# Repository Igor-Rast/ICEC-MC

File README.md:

# ICEC-MC
ICEC-MC Cape for BeagleBone Black

## Introduction
ICEC-MC is a project to create the plans, prototype board and software for a completly Open Source Motor Controller board in the form of a Cape that can be placed on a BeagleBone Black.
The ICEC-MC is build to fit the needs of the FirePick Delta Modular Tool system, Incorporating 4 Modular Tool headers. 
But should also be no problem to handle any other type of 3d printer or CNC machine.

## Project Status

Using Printipi (thanks Collin) the basic driver for moving the FirePickDelta is working. 
G1 commands are beeing performed correctly, G2 and a look ahead function are the next on the line to get fixed.
The calculations for the FirePick seems proven and i am now turning to the BBB for more pins so we can connect the neccecary for our project.
also an graphical user interface would be nice. 

+ idea  
- schematic / logic
- match pinouts
- board layout
- proto run
- debug

### Features

##### 4 endstop connection (x,y,z axis + Bed Level switch)
- configurable as opto or switch type(pull up)

##### 4 FirePick Delta EAT Modular Tool Headers ( new design +2p)
- new 18 pin header for EAT Modular Tool board to include Stepper VRef & BBB_ADC_GND 
- Old 16p EAT tool should work without problems, just dont populate the Termistor parts. ( wire differently)
 
##### 4 embedded DRV8825 stepper drivers (x,y,z,e)
- Digital Current Control (DAC088S085)
- All DRV8825 stepping modes (full step, half step, 1/4 step, 1/8 step, 1/16 step, 1/32 step).,

##### 4 steppers connection tru Modular Tool Header (one tool at a time)
- Digital Current Control (DAC088S085) (if new EAT tool used)

##### 7 BBB ADC inputs for thermistor 
- 3 on board
- 4 accessable tru Modular Tool Headers

##### 4 Servo connections 
- connect up to 4 servos or ledstrips

##### E-Stop Logic Circuit (Oh shit, Button)
- deactivate all steppers and tools with the push of a button.

##### Imbedded voltage regulators
- 12V step down --> fans , if using 24V on motors
- 5C step down --> beaglebone black and logic

##### I2C controlled standalone PWM controller (PCA9685PW)  
- 3 Enbedded Hi-Power Mosfest (AON6758) e.g. heatbed/hotend/vacuumpump
- 3 Embedded Low-Power Mosfet (NIF5002) e.g. fan/leds
- 4 PWM control of D_Out on Modular Tool Headers
- 6 PWM signals left unused (break these out?/add some status leds?)

##### 40pin Connection for Graphical Interface Expansion using cheap 4.3inch 3.2 TFT LCD modules 
- ssd1962 display driver 
- touch sensor 
- sd card reader

##### Remote on function for ATX powersupply
- turn the ATX PSU on/off using the M81/M82 (single ATX supply)

##### BBB reset button

## Developers
TODO: setup google group
If you'd like to be involved in the development of ICEC-MC, please PM me.

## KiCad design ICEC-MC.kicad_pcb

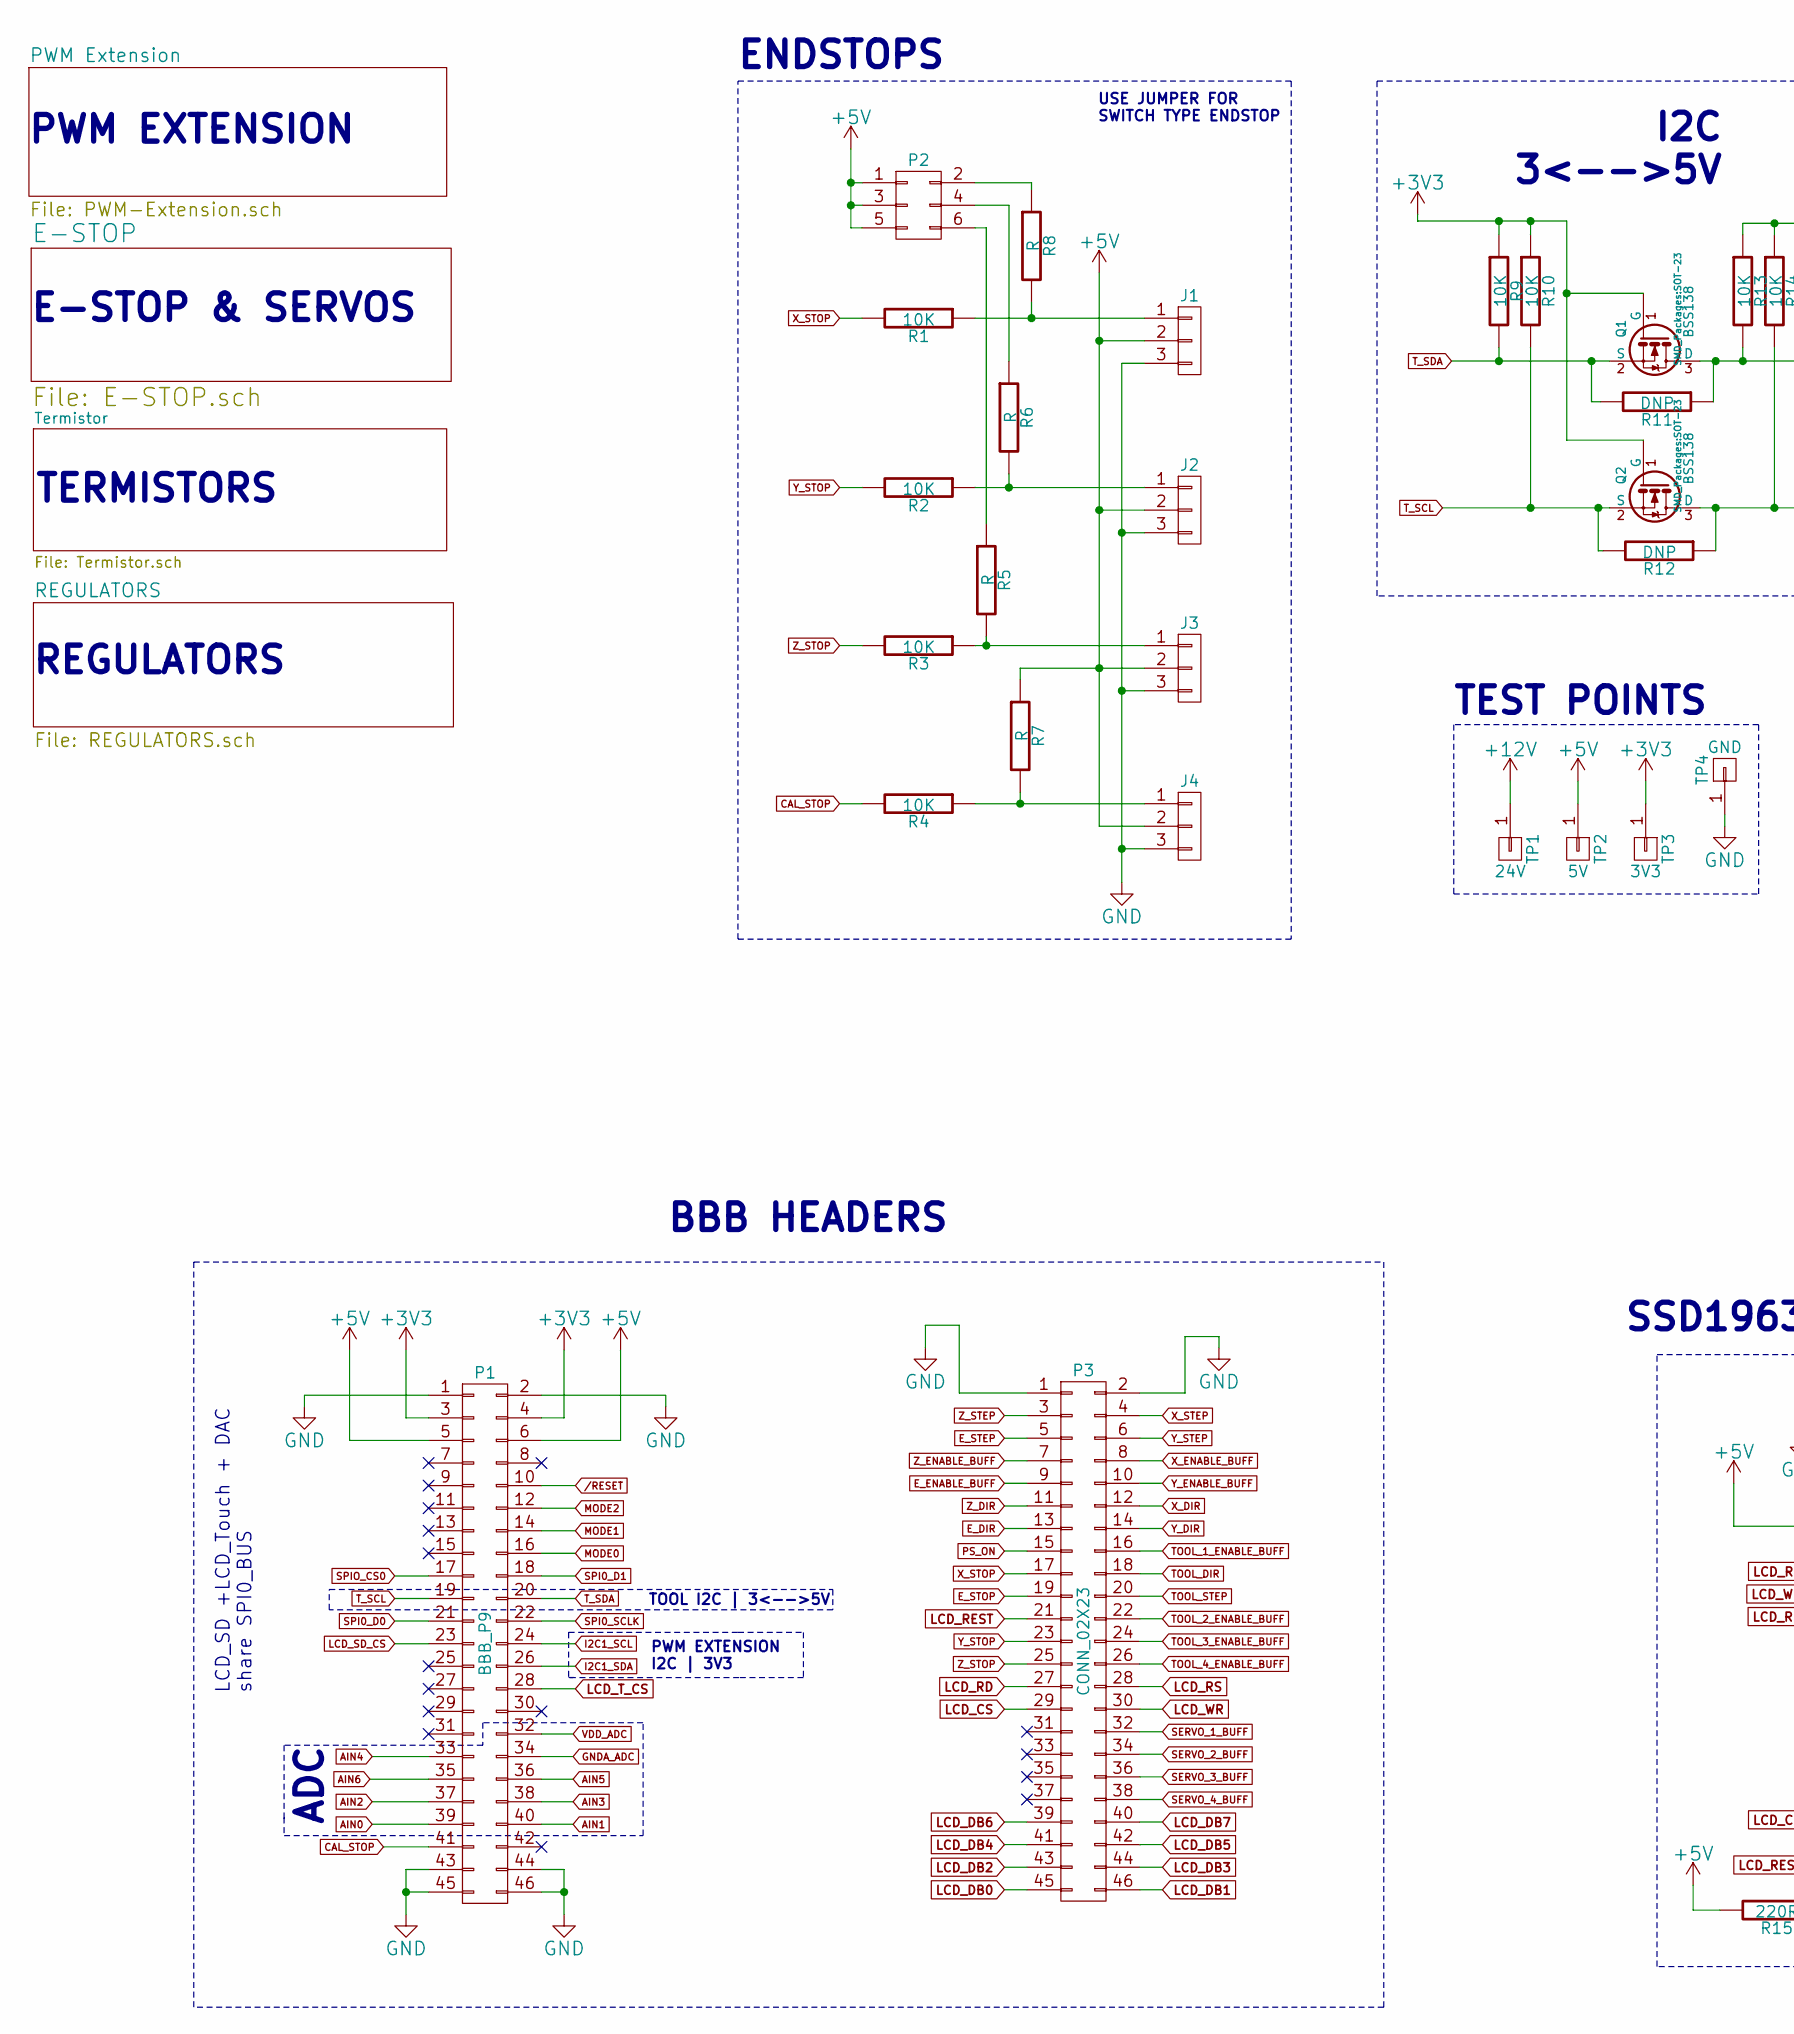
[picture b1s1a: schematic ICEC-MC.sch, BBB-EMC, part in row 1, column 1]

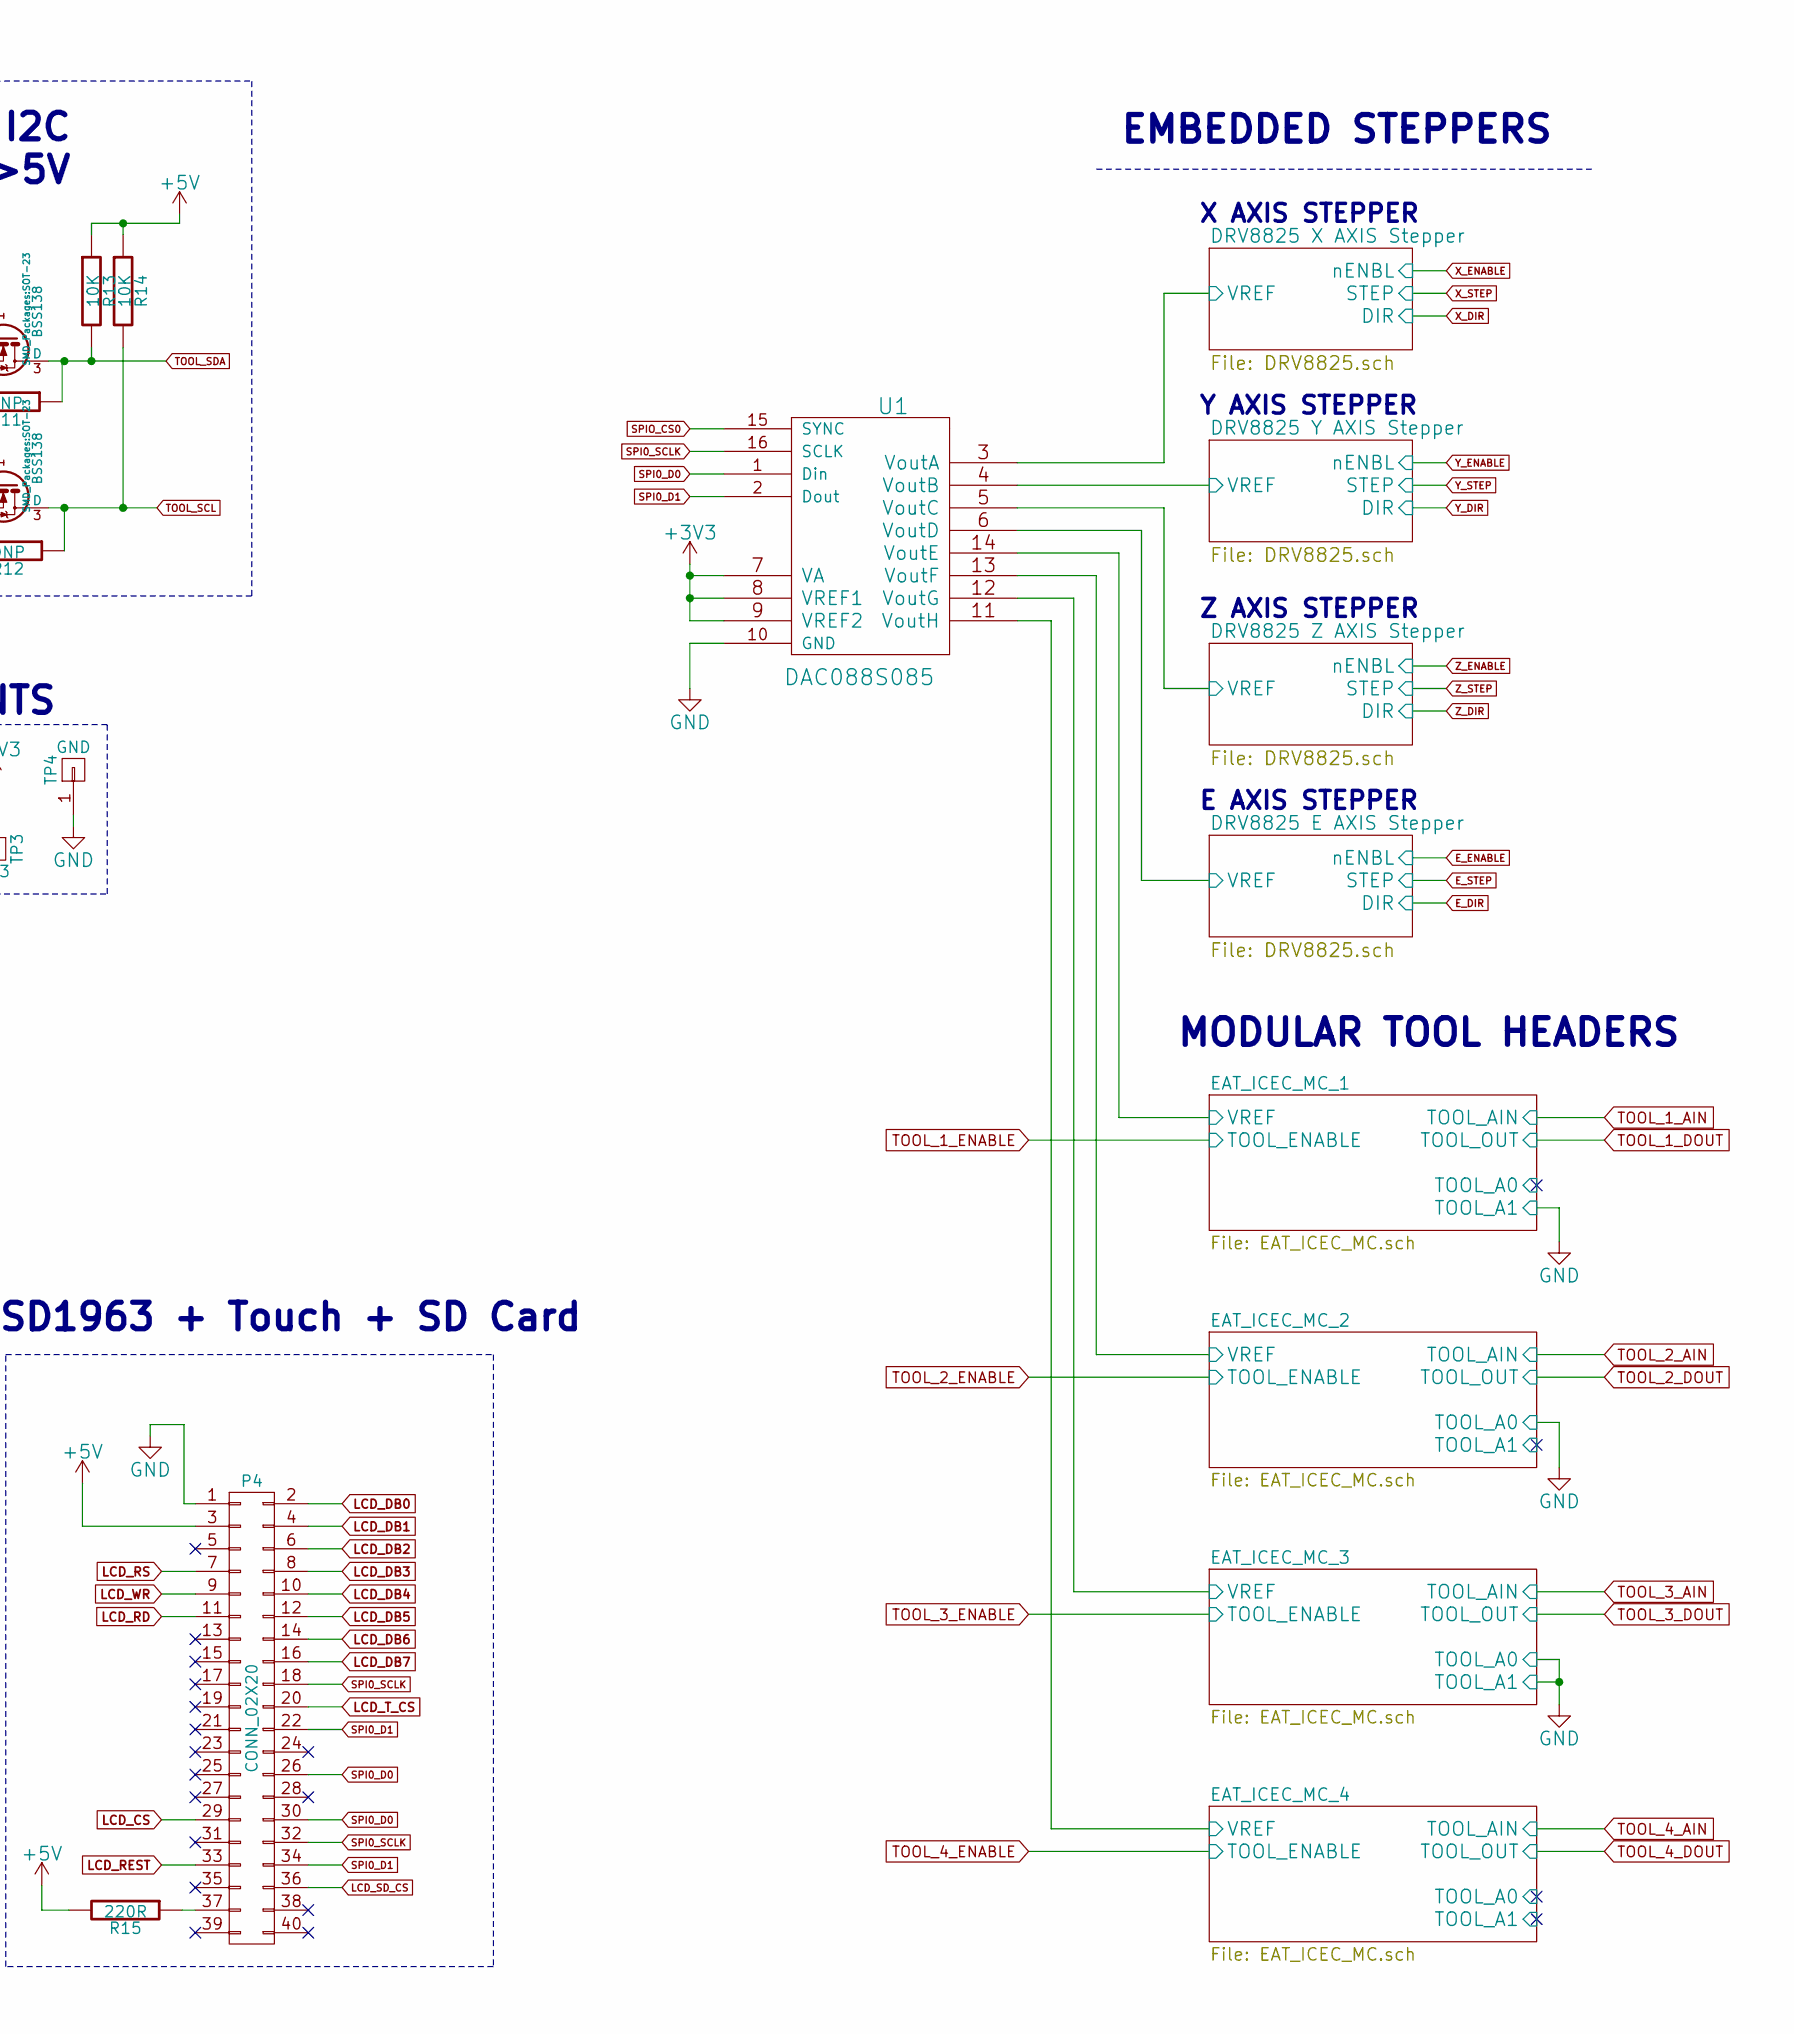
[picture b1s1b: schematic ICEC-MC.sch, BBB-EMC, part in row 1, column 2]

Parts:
J1, J2, J3, J4: CONN_01X03; Socket_Strip_Straight_1x03
P1: BBB_P9; Socket_Strip_Straight_2x23
P2: CONN_02X03; Socket_Strip_Straight_2x03
P3: CONN_02X23; Socket_Strip_Straight_2x23
P4: CONN_02X20; Socket_Strip_Straight_2x20
Q1, Q2: BSS138; SOT-23
R1, R2, R3, R4, R9, R10, R13, R14: 10K; R_0805_HandSoldering
R5, R6, R7, R8: R; R_0805_HandSoldering
R11, R12: DNP; R_0805_HandSoldering
R15: 220R; R_0805_HandSoldering
TP1: 24V; Pin_Header_Straight_1x01
TP2: 5V; Pin_Header_Straight_1x01
TP3: 3V3; Pin_Header_Straight_1x01
TP4: GND; Pin_Header_Straight_1x01
U1: DAC088S085; TSSOP-16_4.4x5mm_Pitch0.65mm

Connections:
+3V3: P1.3, P1.4, Q1.1 (G), Q2.1 (G), R9.1, R10.1, TP3.1, U1.7 (VA), U1.8 (VREF1), U1.9 (VREF2); also elsewhere on the board
+5V: J1.2, J2.2, J3.2, J4.2, P1.5, P1.6, P2.1, P2.3, P2.5, P4.3, R7.1, R13.1, R14.1, R15.2, TP2.1; also elsewhere on the board
/DRV8825 E AXIS Stepper/VREF: U1.6 (VoutD); also elsewhere on the board
/DRV8825 X AXIS Stepper/VREF: U1.3 (VoutA); also elsewhere on the board
/DRV8825 Y AXIS Stepper/VREF: U1.4 (VoutB); also elsewhere on the board
/DRV8825 Z AXIS Stepper/VREF: U1.5 (VoutC); also elsewhere on the board
/EAT_ICEC_MC_1/VREF: U1.14 (VoutE); also elsewhere on the board
/EAT_ICEC_MC_2/VREF: U1.13 (VoutF); also elsewhere on the board
/EAT_ICEC_MC_3/VREF: U1.12 (VoutG); also elsewhere on the board
/EAT_ICEC_MC_4/VREF: U1.11 (VoutH); also elsewhere on the board
/RESET: P1.10
AIN0: P1.39; also elsewhere on the board
AIN1: P1.40; also elsewhere on the board
AIN2: P1.37; also elsewhere on the board
AIN3: P1.38; also elsewhere on the board
AIN4: P1.33; also elsewhere on the board
AIN5: P1.36; also elsewhere on the board
AIN6: P1.35; also elsewhere on the board
CAL_STOP: P1.41, R4.2
E_DIR: P3.13; also elsewhere on the board
E_ENABLE_BUFF: P3.9; also elsewhere on the board
E_STEP: P3.5; also elsewhere on the board
E_STOP: P3.19
GNDA_ADC: P1.34; also elsewhere on the board
I2C1_SCL: P1.24; also elsewhere on the board
I2C1_SDA: P1.26; also elsewhere on the board
LCD_CS: P3.29, P4.29
LCD_DB0: P3.45, P4.2
LCD_DB1: P3.46, P4.4
LCD_DB2: P3.43, P4.6
LCD_DB3: P3.44, P4.8
LCD_DB4: P3.41, P4.10
LCD_DB5: P3.42, P4.12
LCD_DB6: P3.39, P4.14
LCD_DB7: P3.40, P4.16
LCD_RD: P3.27, P4.11
LCD_REST: P3.21, P4.33
LCD_RS: P3.28, P4.7
LCD_SD_CS: P1.23, P4.36
LCD_T_CS: P1.28, P4.20
LCD_WR: P3.30, P4.9
MODE0: P1.16; also elsewhere on the board
MODE1: P1.14; also elsewhere on the board
MODE2: P1.12; also elsewhere on the board
unnamed: J1.1, R1.1, R8.2
unnamed: J2.1, R2.1, R6.2
unnamed: J3.1, R3.1, R5.2
unnamed: J4.1, R4.1, R7.2
unnamed: P2.2, R8.1
unnamed: P2.4, R6.1
unnamed: P2.6, R5.1
unnamed: P4.37, R15.1
PS_ON: P3.15; also elsewhere on the board
SERVO_1_BUFF: P3.32; also elsewhere on the board
SERVO_2_BUFF: P3.34; also elsewhere on the board
SERVO_3_BUFF: P3.36; also elsewhere on the board
SERVO_4_BUFF: P3.38; also elsewhere on the board
SPI0_D0: P1.21, P4.26, P4.30, U1.1 (Din)
SPI0_D1: P1.18, P4.22, P4.34, U1.2 (Dout)
SPI0_SCLK: P1.22, P4.18, P4.32, U1.16 (SCLK)
SPIO_CS0: P1.17, U1.15 (SYNC)
TOOL_1_ENABLE_BUFF: P3.16; also elsewhere on the board
TOOL_2_ENABLE_BUFF: P3.22; also elsewhere on the board
TOOL_3_ENABLE_BUFF: P3.24; also elsewhere on the board
TOOL_4_ENABLE_BUFF: P3.26; also elsewhere on the board
TOOL_DIR: P3.18; also elsewhere on the board
TOOL_SCL: Q2.3 (D), R12.1, R14.2; also elsewhere on the board
TOOL_SDA: Q1.3 (D), R11.1, R13.2; also elsewhere on the board
TOOL_STEP: P3.20; also elsewhere on the board
T_SCL: P1.19, Q2.2 (S), R10.2, R12.2
T_SDA: P1.20, Q1.2 (S), R9.2, R11.2
VDD_ADC: P1.32; also elsewhere on the board
X_DIR: P3.12; also elsewhere on the board
X_ENABLE_BUFF: P3.8; also elsewhere on the board
X_STEP: P3.4; also elsewhere on the board
X_STOP: P3.17, R1.2
Y_DIR: P3.14; also elsewhere on the board
Y_ENABLE_BUFF: P3.10; also elsewhere on the board
Y_STEP: P3.6; also elsewhere on the board
Y_STOP: P3.23, R2.2
Z_DIR: P3.11; also elsewhere on the board
Z_ENABLE_BUFF: P3.7; also elsewhere on the board
Z_STEP: P3.3; also elsewhere on the board
Z_STOP: P3.25, R3.2

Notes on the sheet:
ENDSTOPS
X AXIS STEPPER
Y AXIS STEPPER
EMBEDDED STEPPERS
Z AXIS STEPPER
E AXIS STEPPER
E-STOP & SERVOS
MODULAR TOOL HEADERS
SSD1963 + Touch + SD Card
LCD_SD +LCD_Touch + DAC share SPI0_BUS
BBB HEADERS
TOOL I2C | 3<-->5V
PWM EXTENSION
USE JUMPER FOR SWITCH TYPE ENDSTOP
ADC
TERMISTORS
I2C 3<-->5V
REGULATORS
TEST POINTS
PWM EXTENSION I2C | 3V3

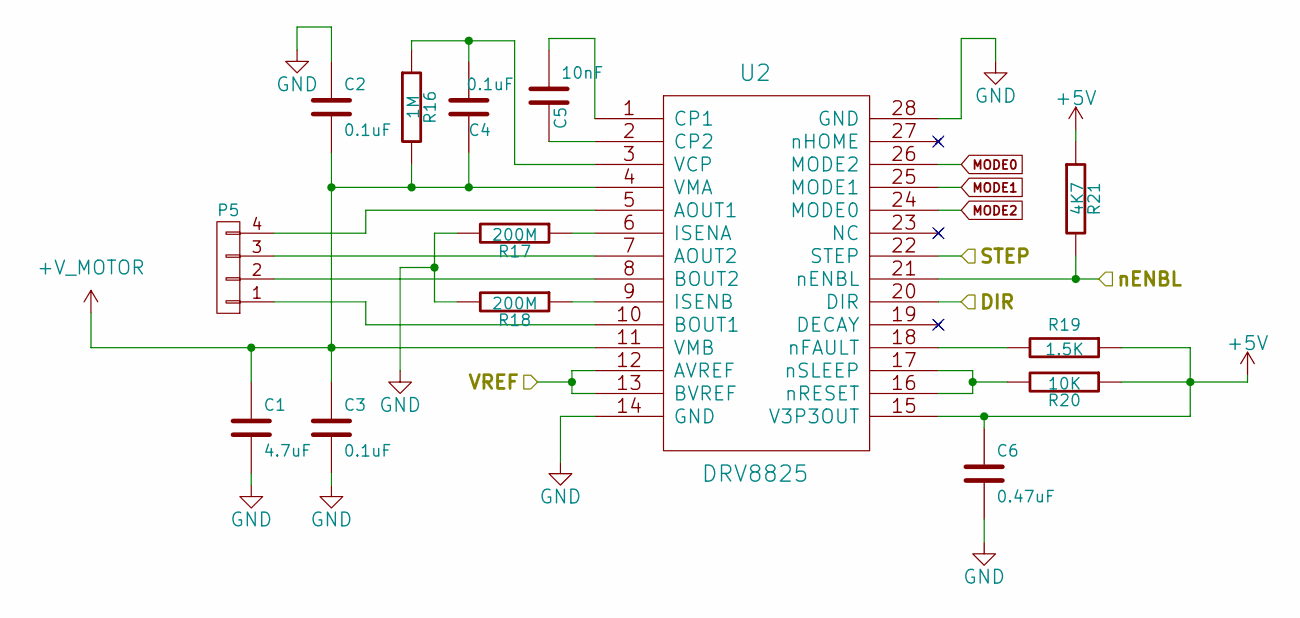
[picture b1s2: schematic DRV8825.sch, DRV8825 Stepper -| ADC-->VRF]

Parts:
C1: 4.7uF; C_0805_HandSoldering
C2, C3, C4: 0.1uF; C_0805_HandSoldering
C5: 10nF; C_0805_HandSoldering
C6: 0.47uF; C_0805_HandSoldering
P5: CONN_01X04; Socket_Strip_Straight_1x04
R16: 1M; R_0805_HandSoldering
R17, R18: 200M; R_0805_HandSoldering
R19: 1.5K; R_0805_HandSoldering
R20: 10K; R_0805_HandSoldering
R21: 4K7; R_0805_HandSoldering
U2: DRV8825; SOJ-32

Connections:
+5V: C6.1, R19.1, R20.1, R21.1, U2.15 (V3P3OUT); also elsewhere on the board
+V_MOTOR: C1.1, C2.2, C3.1, C4.1, R16.2, U2.4 (VMA), U2.11 (VMB); also elsewhere on the board
/DRV8825 X AXIS Stepper/VREF: U2.12 (AVREF), U2.13 (BVREF); also elsewhere on the board
MODE0: U2.26 (MODE2); also elsewhere on the board
MODE1: U2.25 (MODE1); also elsewhere on the board
MODE2: U2.24 (MODE0); also elsewhere on the board
unnamed: C4.2, R16.1, U2.3 (VCP)
unnamed: C5.1, U2.1 (CP1)
unnamed: C5.2, U2.2 (CP2)
unnamed: P5.1, U2.10 (BOUT1)
unnamed: P5.2, U2.8 (BOUT2)
unnamed: P5.3, U2.7 (AOUT2)
unnamed: P5.4, U2.5 (AOUT1)
unnamed: R17.1, U2.6 (ISENA)
unnamed: R18.1, U2.9 (ISENB)
unnamed: R19.2, U2.18 (nFAULT)
unnamed: R20.2, U2.16 (nRESET), U2.17 (nSLEEP)
X_DIR: U2.20 (DIR); also elsewhere on the board
X_ENABLE: R21.2, U2.21 (nENBL); also elsewhere on the board
X_STEP: U2.22 (STEP); also elsewhere on the board

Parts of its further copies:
C7, C13, C19: 4.7uF; C_0805_HandSoldering
C8, C9, C10, C14, C15, C16, C20, C21, C22: 0.1uF; C_0805_HandSoldering
C11, C17, C23: 10nF; C_0805_HandSoldering
C12, C18, C24: 0.47uF; C_0805_HandSoldering
P11, P12, P13: CONN_01X04; Socket_Strip_Straight_1x04
R32, R38, R44: 1M; R_0805_HandSoldering
R33, R34, R39, R40, R45, R46: 200M; R_0805_HandSoldering
R35, R41, R47: 1.5K; R_0805_HandSoldering
R36, R42, R48: 10K; R_0805_HandSoldering
R37, R43, R49: 4K7; R_0805_HandSoldering
U5, U6, U7: DRV8825; SOJ-32

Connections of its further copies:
+5V: C12.1, C18.1, C24.1, R35.1, R36.1, R37.1, R41.1, R42.1, R43.1, R47.1, R48.1, R49.1, U5.15 (V3P3OUT), U6.15 (V3P3OUT), U7.15 (V3P3OUT); also elsewhere on the board
+V_MOTOR: C7.1, C8.2, C9.1, C10.1, C13.1, C14.2, C15.1, C16.1, C19.1, C20.2, C21.1, C22.1, R32.2, R38.2, R44.2, U5.4 (VMA), U5.11 (VMB), U6.4 (VMA), U6.11 (VMB), U7.4 (VMA), U7.11 (VMB); also elsewhere on the board
/DRV8825 E AXIS Stepper/VREF: U7.12 (AVREF), U7.13 (BVREF); also elsewhere on the board
/DRV8825 Y AXIS Stepper/VREF: U5.12 (AVREF), U5.13 (BVREF); also elsewhere on the board
/DRV8825 Z AXIS Stepper/VREF: U6.12 (AVREF), U6.13 (BVREF); also elsewhere on the board
E_DIR: U7.20 (DIR); also elsewhere on the board
E_ENABLE: R49.2, U7.21 (nENBL); also elsewhere on the board
E_STEP: U7.22 (STEP); also elsewhere on the board
MODE0: U5.26 (MODE2), U6.26 (MODE2), U7.26 (MODE2); also elsewhere on the board
MODE1: U5.25 (MODE1), U6.25 (MODE1), U7.25 (MODE1); also elsewhere on the board
MODE2: U5.24 (MODE0), U6.24 (MODE0), U7.24 (MODE0); also elsewhere on the board
unnamed: C10.2, R32.1, U5.3 (VCP)
unnamed: C11.1, U5.1 (CP1)
unnamed: C11.2, U5.2 (CP2)
unnamed: C16.2, R38.1, U6.3 (VCP)
unnamed: C17.1, U6.1 (CP1)
unnamed: C17.2, U6.2 (CP2)
unnamed: C22.2, R44.1, U7.3 (VCP)
unnamed: C23.1, U7.1 (CP1)
unnamed: C23.2, U7.2 (CP2)
unnamed: P11.1, U5.10 (BOUT1)
unnamed: P11.2, U5.8 (BOUT2)
unnamed: P11.3, U5.7 (AOUT2)
unnamed: P11.4, U5.5 (AOUT1)
unnamed: P12.1, U6.10 (BOUT1)
unnamed: P12.2, U6.8 (BOUT2)
unnamed: P12.3, U6.7 (AOUT2)
unnamed: P12.4, U6.5 (AOUT1)
unnamed: P13.1, U7.10 (BOUT1)
unnamed: P13.2, U7.8 (BOUT2)
unnamed: P13.3, U7.7 (AOUT2)
unnamed: P13.4, U7.5 (AOUT1)
unnamed: R33.1, U5.6 (ISENA)
unnamed: R34.1, U5.9 (ISENB)
unnamed: R35.2, U5.18 (nFAULT)
unnamed: R36.2, U5.16 (nRESET), U5.17 (nSLEEP)
unnamed: R39.1, U6.6 (ISENA)
unnamed: R40.1, U6.9 (ISENB)
unnamed: R41.2, U6.18 (nFAULT)
unnamed: R42.2, U6.16 (nRESET), U6.17 (nSLEEP)
unnamed: R45.1, U7.6 (ISENA)
unnamed: R46.1, U7.9 (ISENB)
unnamed: R47.2, U7.18 (nFAULT)
unnamed: R48.2, U7.16 (nRESET), U7.17 (nSLEEP)
Y_DIR: U5.20 (DIR); also elsewhere on the board
Y_ENABLE: R37.2, U5.21 (nENBL); also elsewhere on the board
Y_STEP: U5.22 (STEP); also elsewhere on the board
Z_DIR: U6.20 (DIR); also elsewhere on the board
Z_ENABLE: R43.2, U6.21 (nENBL); also elsewhere on the board
Z_STEP: U6.22 (STEP); also elsewhere on the board

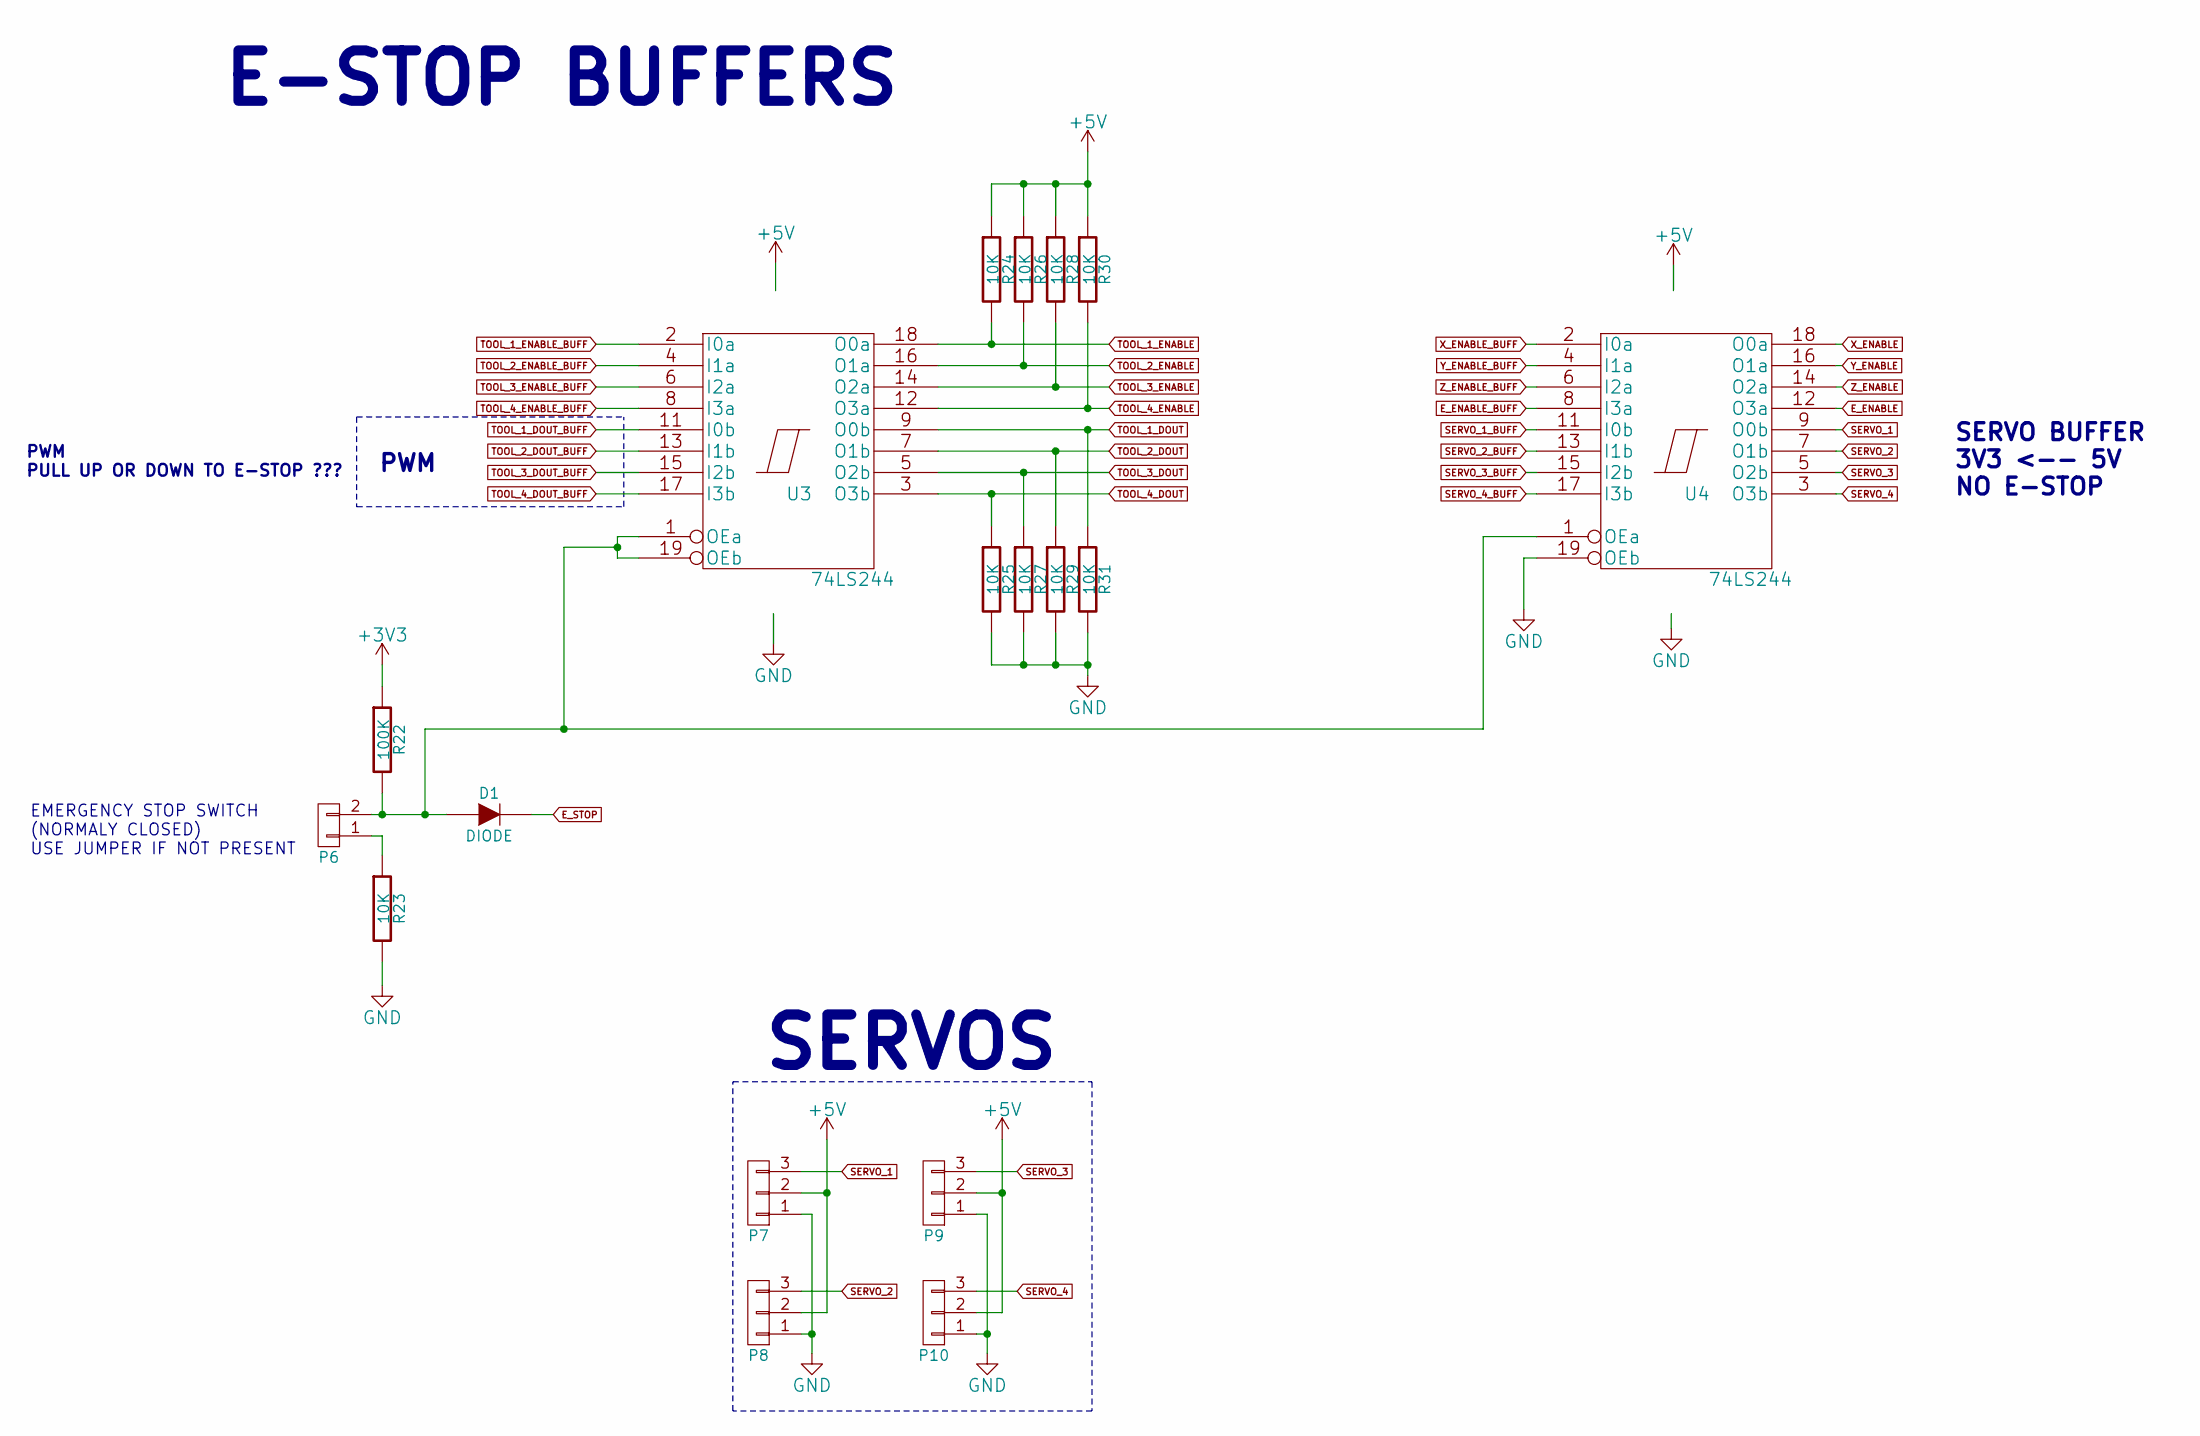
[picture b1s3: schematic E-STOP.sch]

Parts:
D1: DIODE
P6: CONN_01X02; Socket_Strip_Straight_1x02
P7, P8, P9, P10: CONN_01X03; Socket_Strip_Straight_1x03
R22: 100K; R_0805_HandSoldering
R23, R24, R25, R26, R27, R28, R29, R30, R31: 10K; R_0805_HandSoldering
U3, U4: 74LS244; SSOP-20

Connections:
+3V3: R22.1; also elsewhere on the board
+5V: P7.2, P8.2, P9.2, P10.2, R24.1, R26.1, R28.1, R30.1; also elsewhere on the board
E_ENABLE: U4.12 (O3a); also elsewhere on the board
E_ENABLE_BUFF: U4.8 (I3a); also elsewhere on the board
unnamed: D1.1 (A), P6.2, R22.2, U3.1 (OEa), U3.19 (OEb), U4.1 (OEa)
unnamed: P6.1, R23.1
SERVO_1: P7.3, U4.9 (O0b)
SERVO_1_BUFF: U4.11 (I0b); also elsewhere on the board
SERVO_2: P8.3, U4.7 (O1b)
SERVO_2_BUFF: U4.13 (I1b); also elsewhere on the board
SERVO_3: P9.3, U4.5 (O2b)
SERVO_3_BUFF: U4.15 (I2b); also elsewhere on the board
SERVO_4: P10.3, U4.3 (O3b)
SERVO_4_BUFF: U4.17 (I3b); also elsewhere on the board
TOOL_1_DOUT: R31.1, U3.9 (O0b); also elsewhere on the board
TOOL_1_DOUT_BUFF: U3.11 (I0b); also elsewhere on the board
TOOL_1_ENABLE: R24.2, U3.18 (O0a); also elsewhere on the board
TOOL_1_ENABLE_BUFF: U3.2 (I0a); also elsewhere on the board
TOOL_2_DOUT: R29.1, U3.7 (O1b); also elsewhere on the board
TOOL_2_DOUT_BUFF: U3.13 (I1b); also elsewhere on the board
TOOL_2_ENABLE: R26.2, U3.16 (O1a); also elsewhere on the board
TOOL_2_ENABLE_BUFF: U3.4 (I1a); also elsewhere on the board
TOOL_3_DOUT: R27.1, U3.5 (O2b); also elsewhere on the board
TOOL_3_DOUT_BUFF: U3.15 (I2b); also elsewhere on the board
TOOL_3_ENABLE: R28.2, U3.14 (O2a); also elsewhere on the board
TOOL_3_ENABLE_BUFF: U3.6 (I2a); also elsewhere on the board
TOOL_4_DOUT: R25.1, U3.3 (O3b); also elsewhere on the board
TOOL_4_DOUT_BUFF: U3.17 (I3b); also elsewhere on the board
TOOL_4_ENABLE: R30.2, U3.12 (O3a); also elsewhere on the board
TOOL_4_ENABLE_BUFF: U3.8 (I3a); also elsewhere on the board
VCC: U3.20 (VCC), U4.20 (VCC)
X_ENABLE: U4.18 (O0a); also elsewhere on the board
X_ENABLE_BUFF: U4.2 (I0a); also elsewhere on the board
Y_ENABLE: U4.16 (O1a); also elsewhere on the board
Y_ENABLE_BUFF: U4.4 (I1a); also elsewhere on the board
Z_ENABLE: U4.14 (O2a); also elsewhere on the board
Z_ENABLE_BUFF: U4.6 (I2a); also elsewhere on the board

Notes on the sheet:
EMERGENCY STOP SWITCH (NORMALY CLOSED) USE JUMPER IF NOT PRESENT
PWM
PWM PULL UP OR DOWN TO E-STOP ???
SERVO BUFFER 3V3 <-- 5V NO E-STOP
SERVOS
E-STOP BUFFERS

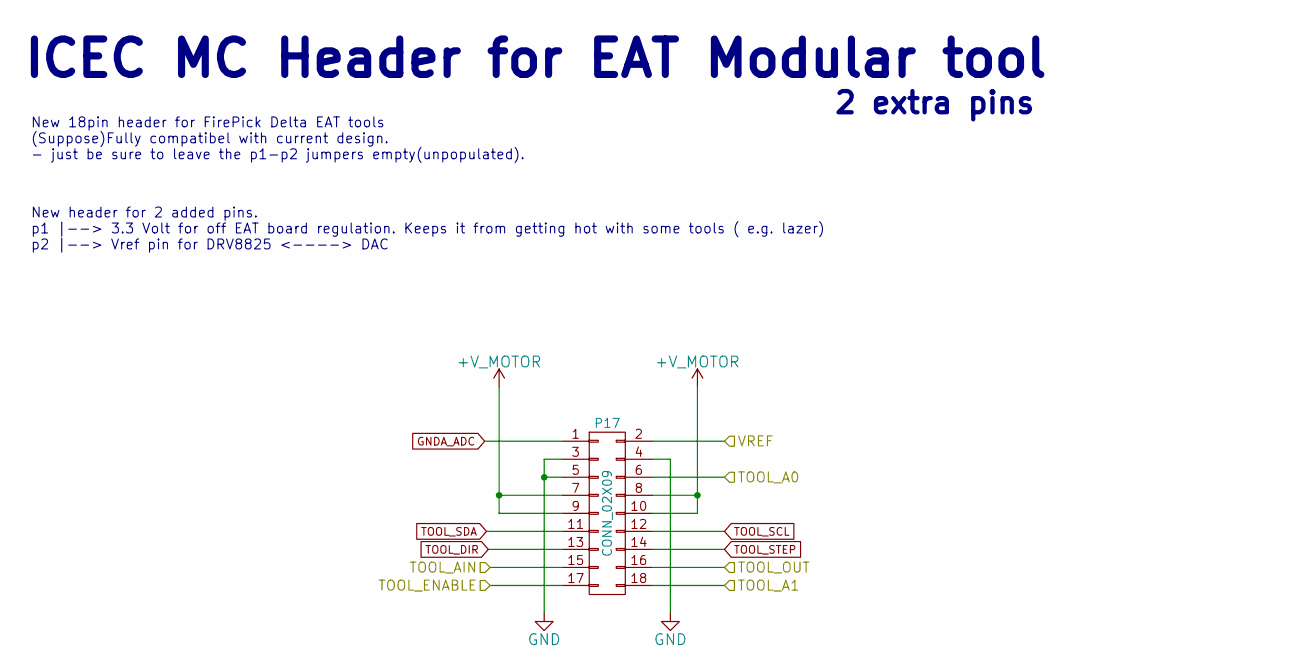
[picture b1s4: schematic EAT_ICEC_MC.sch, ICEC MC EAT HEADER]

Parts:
P14: CONN_02X09; Socket_Strip_Straight_2x09

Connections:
+V_MOTOR: P14.7, P14.8, P14.9, P14.10; also elsewhere on the board
/EAT_ICEC_MC_1/TOOL_A0: P14.6
/EAT_ICEC_MC_1/VREF: P14.2; also elsewhere on the board
GNDA_ADC: P14.1; also elsewhere on the board
TOOL_1_AIN: P14.15; also elsewhere on the board
TOOL_1_DOUT: P14.16; also elsewhere on the board
TOOL_1_ENABLE: P14.17; also elsewhere on the board
TOOL_DIR: P14.13; also elsewhere on the board
TOOL_SCL: P14.12; also elsewhere on the board
TOOL_SDA: P14.11; also elsewhere on the board
TOOL_STEP: P14.14; also elsewhere on the board

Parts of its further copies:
P15, P16, P17: CONN_02X09; Socket_Strip_Straight_2x09

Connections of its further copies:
+V_MOTOR: P15.7, P15.8, P15.9, P15.10, P16.7, P16.8, P16.9, P16.10, P17.7, P17.8, P17.9, P17.10; also elsewhere on the board
/EAT_ICEC_MC_2/TOOL_A1: P15.18
/EAT_ICEC_MC_2/VREF: P15.2; also elsewhere on the board
/EAT_ICEC_MC_3/VREF: P16.2; also elsewhere on the board
/EAT_ICEC_MC_4/TOOL_A0: P17.6
/EAT_ICEC_MC_4/TOOL_A1: P17.18
/EAT_ICEC_MC_4/VREF: P17.2; also elsewhere on the board
GNDA_ADC: P15.1, P16.1, P17.1; also elsewhere on the board
TOOL_2_AIN: P15.15; also elsewhere on the board
TOOL_2_DOUT: P15.16; also elsewhere on the board
TOOL_2_ENABLE: P15.17; also elsewhere on the board
TOOL_3_AIN: P16.15; also elsewhere on the board
TOOL_3_DOUT: P16.16; also elsewhere on the board
TOOL_3_ENABLE: P16.17; also elsewhere on the board
TOOL_4_AIN: P17.15; also elsewhere on the board
TOOL_4_DOUT: P17.16; also elsewhere on the board
TOOL_4_ENABLE: P17.17; also elsewhere on the board
TOOL_DIR: P15.13, P16.13, P17.13; also elsewhere on the board
TOOL_SCL: P15.12, P16.12, P17.12; also elsewhere on the board
TOOL_SDA: P15.11, P16.11, P17.11; also elsewhere on the board
TOOL_STEP: P15.14, P16.14, P17.14; also elsewhere on the board

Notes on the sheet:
New 18pin header for FirePick Delta EAT tools (Suppose)Fully compatibel with current design. - just be sure to leave the p1-p2 jumpers empty(unpopulated).
New header for 2 added pins. p1 |--> 3.3 Volt for off EAT board regulation. Keeps it from getting hot with some tools ( e.g. lazer) p2 |--> Vref pin for DRV8825 <----> DAC
ICEC MC Header for EAT Modular tool
2 extra pins
